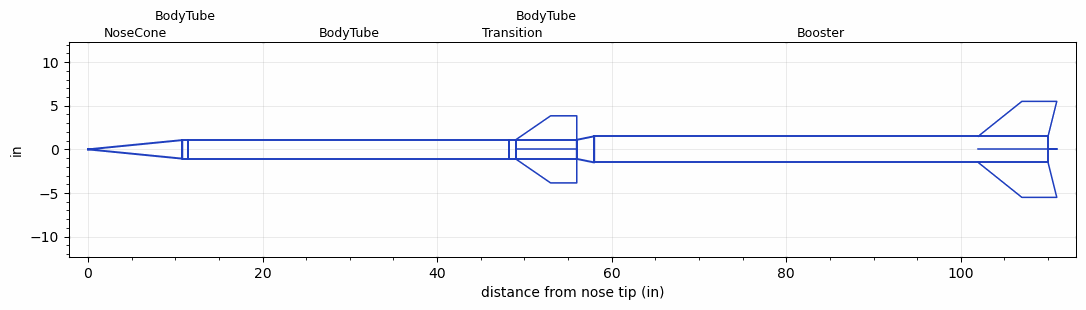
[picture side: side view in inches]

<RASAeroDocument>
 <FileVersion>2</FileVersion>
 <RocketDesign>
  <NoseCone>
   <Length>10.8</Length>
   <Diameter>2.125</Diameter>
   <Shape>Conical</Shape>
   <BluntRadius>0.02</BluntRadius>
   <Location>0</Location>
  </NoseCone>
  <BodyTube>
   <Length>0.7</Length>
   <Diameter>2.125</Diameter>
   <Location>10.8</Location>
  </BodyTube>
  <BodyTube>
   <Length>36.7499</Length>
   <Diameter>2.125</Diameter>
   <Location>11.5</Location>
  </BodyTube>
  <Transition>
   <Length>0.75</Length>
   <Diameter>2.185</Diameter>
   <Location>48.2499</Location>
   <RearDiameter>2.185</RearDiameter>
  </Transition>
  <BodyTube>
   <Length>7</Length>
   <Diameter>2.185</Diameter>
   <Location>48.9999</Location>
   <Fin>
    <Count>4</Count>
    <Chord>7</Chord>
    <Span>2.75</Span>
    <SweepDistance>4</SweepDistance>
    <TipChord>3</TipChord>
    <Thickness>0.125</Thickness>
    <LERadius>0.02</LERadius>
    <Location>7</Location>
    <AirfoilSection>Double Wedge</AirfoilSection>
    <FX1>1.5</FX1>
   </Fin>
  </BodyTube>
  <Booster>
   <Length>51.9999</Length>
   <Diameter>3</Diameter>
   <InsideDiameter>2.185</InsideDiameter>
   <Location>55.9999</Location>
   <ShoulderLength>2</ShoulderLength>
   <Fin>
    <Count>4</Count>
    <Chord>8</Chord>
    <Span>4</Span>
    <SweepDistance>5</SweepDistance>
    <TipChord>4</TipChord>
    <Thickness>0.1875</Thickness>
    <LERadius>0.05</LERadius>
    <Location>8</Location>
    <AirfoilSection>Hexagonal</AirfoilSection>
    <FX1>1</FX1>
    <FX3>1</FX3>
   </Fin>
  </Booster>
  <Surface>Rough Camouflage Paint</Surface>
  <ModifiedBarrowman>False</ModifiedBarrowman>
  <Turbulence>False</Turbulence>
  <UseBooster1>True</UseBooster1>
  <UseBooster2>False</UseBooster2>
 </RocketDesign>
 <LaunchSite>
  <Altitude>0</Altitude>
  <Pressure>29.9214</Pressure>
  <RodAngle>0</RodAngle>
  <RodLength>7</RodLength>
  <Temperature>59</Temperature>
  <WindSpeed>4.4739</WindSpeed>
 </LaunchSite>
 <Recovery>
  <Altitude1>0</Altitude1>
  <Altitude2>0</Altitude2>
  <DeviceType1>None</DeviceType1>
  <DeviceType2>None</DeviceType2>
  <Event1>False</Event1>
  <Event2>False</Event2>
  <Size1>0</Size1>
  <Size2>0</Size2>
  <EventType1>None</EventType1>
  <EventType2>None</EventType2>
  <CD1>0</CD1>
  <CD2>0</CD2>
 </Recovery>
 <SimulationList>
  <Simulation>
   <SustainerEngine>L3258  (AeroTech)</SustainerEngine>
   <SustainerLaunchWt>9.38</SustainerLaunchWt>
   <SustainerNozzleDiameter>2</SustainerNozzleDiameter>
   <SustainerCG>31.54</SustainerCG>
   <SustainerIgnitionDelay>1</SustainerIgnitionDelay>
   <Booster1Engine>N6154  (AeroTech)</Booster1Engine>
   <Booster1LaunchWt>30.82</Booster1LaunchWt>
   <Booster1SeparationDelay>0</Booster1SeparationDelay>
   <Booster1IgnitionDelay>0</Booster1IgnitionDelay>
   <Booster1CG>68.41</Booster1CG>
   <Booster1NozzleDiameter>3</Booster1NozzleDiameter>
   <IncludeBooster1>True</IncludeBooster1>
   <Booster2Delay>0</Booster2Delay>
   <IncludeBooster2>False</IncludeBooster2>
   <TimetoApogee>51.91759</TimetoApogee>
   <MaxAltitude>66008.22</MaxAltitude>
   <MaxVelocity>5653.172</MaxVelocity>
  </Simulation>
 </SimulationList>
</RASAeroDocument>
